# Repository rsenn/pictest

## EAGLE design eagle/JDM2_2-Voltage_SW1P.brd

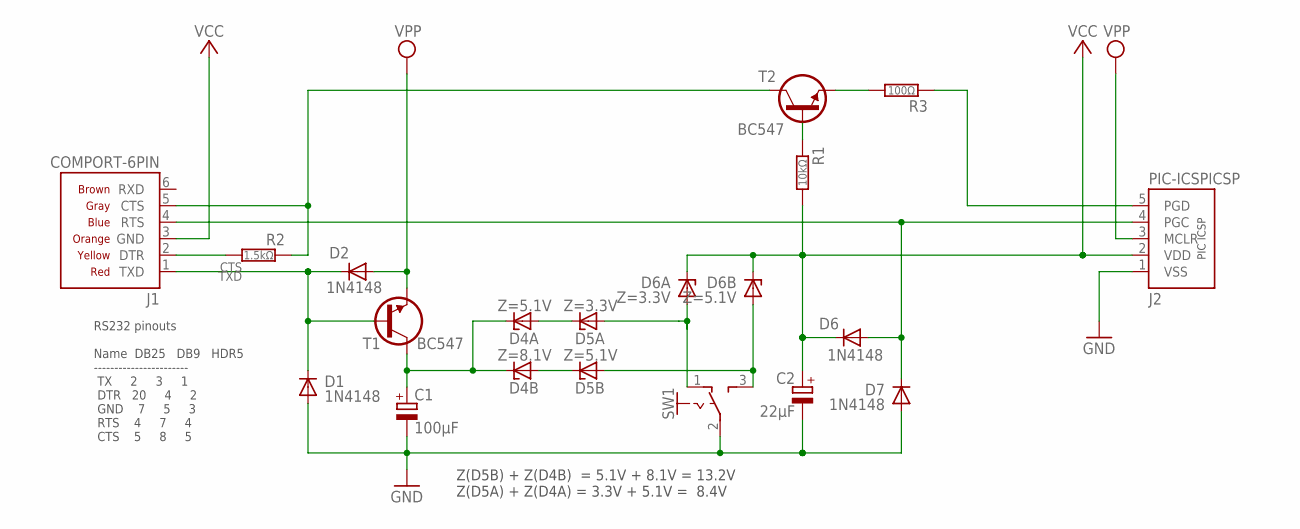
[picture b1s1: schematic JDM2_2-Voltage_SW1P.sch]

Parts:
C1: 100μF; E2,5-5
C2: 22μF; E2,5-4
D1, D6, D7: 1N4148; DO34-5V
D2: 1N4148; DO34-5
D4A, D5B: Z=5.1V; DO34Z5
D4B: Z=8.1V; DO34Z5
D5A: Z=3.3V; DO34Z5
D6A: Z=3.3V; DO34Z7V
D6B: Z=5.1V; DO34Z7V
J1: COMPORT-6PIN; RS232-6PIN
J2: PIC-ICSPICSP; PIC-ICSP
R1: 10kΩ; 0202/7-V
R2: 1.5kΩ; 0202/7-V
R3: 100Ω; 0202/10
SW1: SL-SW-1P-2T-H; SLSW-1P2T-H
T1, T2: BC547; TO92-CBE

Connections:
/MCLR: D2.A, J2.3 (MCLR), T1.E
CLK: D6.A, D7.C, J1.4 (RTS), J2.4 (PGC)
CTS: J1.5 (CTS), R2.1, T2.C
DATA: R3.2, T2.E
GND: C1.-, C2.-, D1.A, D7.A, J2.1 (VSS), SW1.2
unnamed: R1.1, T2.B
unnamed: D5A.A, D6A.A, SW1.1 (O)
unnamed: D5B.A, D6B.A, SW1.3 (S)
unnamed: D4A.A, D5A.C
unnamed: D4B.A, D5B.C
unnamed: J1.2 (DTR), R2.2
PGD: J2.5 (PGD), R3.1
TXD: D1.C, D2.C, J1.1 (TXD), T1.B
VCC: C2.+, D6.C, D6A.C, D6B.C, J1.3 (GND), J2.2 (VDD), R1.2
VPP: C1.+, D4A.C, D4B.C, T1.C

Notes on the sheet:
RS232 pinouts Name DB25 DB9 HDR5 ----------------------- TX 2 3 1 DTR 20 4 2 GND 7 5 3 RTS 4 7 4 CTS 5 8 5
Z(D5B) + Z(D4B) = 5.1V + 8.1V = 13.2V Z(D5A) + Z(D4A) = 3.3V + 5.1V = 8.4V

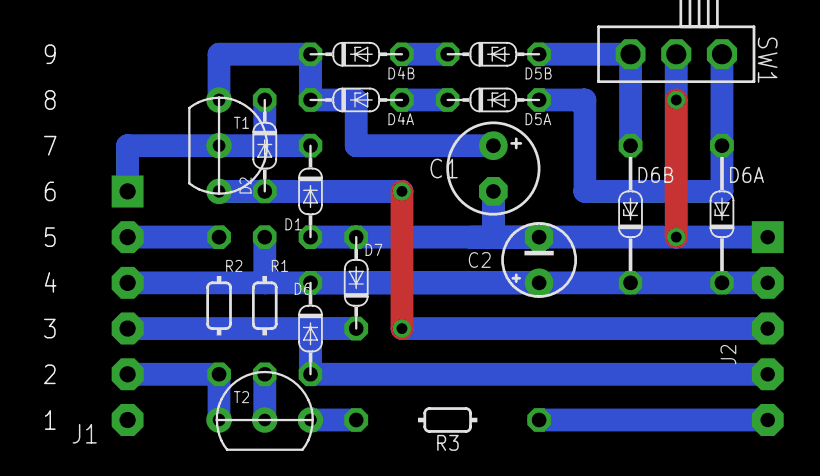
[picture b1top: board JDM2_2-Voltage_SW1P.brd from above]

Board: 2 copper layers, 20 parts (0 on the bottom side), 15 nets.

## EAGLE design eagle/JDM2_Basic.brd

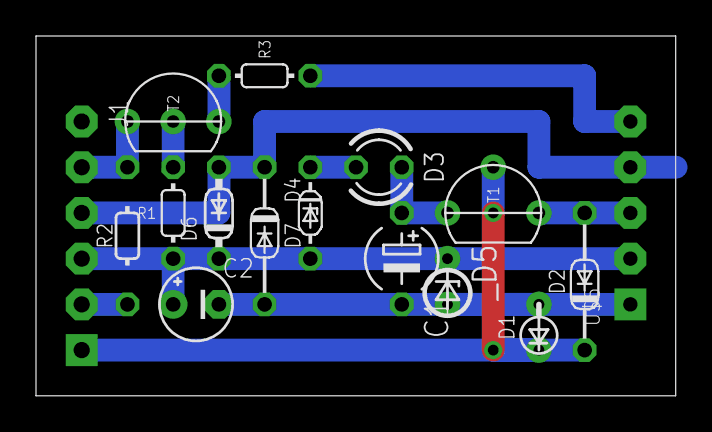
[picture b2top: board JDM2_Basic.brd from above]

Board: 2 copper layers, 35.5 x 20.0 mm, 16 parts (0 on the bottom side), 12 nets.

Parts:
C1: 100μF; E5-4
C2: 22μF; E2,5-4
D1: 1N4148; DO34-2,5-A
D2, D7: 1N4148; DO34-7
D3: Vpp; LED3MM
D4: Z=8.1V; DO34Z5
D6: 1N4148; DO34-5
J1: COMPORT-6PIN; RS232-6PIN
R1: 10kΩ; 0202/5
R2: 1.5kΩ; 0202/7
R3: 100Ω; 0202/5
T1: BC547CBE-A; TO92-CBE-A
T2: BC547CBE; TO92-CBE
U$5: PIC-ICSPICSP; PIC-ICSP
_D5: Z=5.1V; DO35Z2_54

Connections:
/MCLR: D2.A, T1.E, U$5.3
CLK: D6.A, D7.C, J1.4, U$5.4
CTS: J1.5, R2.2, T2.C
DATA: R3.2, T2.E
DTR: J1.2, R2.1
unnamed: R1.1, T2.B
unnamed: D3.K, D4.C
PGD: R3.1, U$5.5
TXD: D1.C, D2.C, J1.1, T1.B
VDD: C2.+, D4.A, D6.C, J1.3, R1.2, U$5.2, _D5.C
VPP: C1.+, D3.A, T1.C
VSS: C1.-, C2.-, D1.A, D7.A, U$5.1, _D5.A
